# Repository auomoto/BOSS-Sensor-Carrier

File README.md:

# BOSS Sensor Carrier
## AD590 and HiH4031 Sensor Carrier
An AD590 temperature sensor and an HiH4031 humidity sensor are mounted on a single carrier board that also has a clearance hole for an 8-32 machine screw. These sensor boards are mounted at various locations inside the BOSS spectrograph.

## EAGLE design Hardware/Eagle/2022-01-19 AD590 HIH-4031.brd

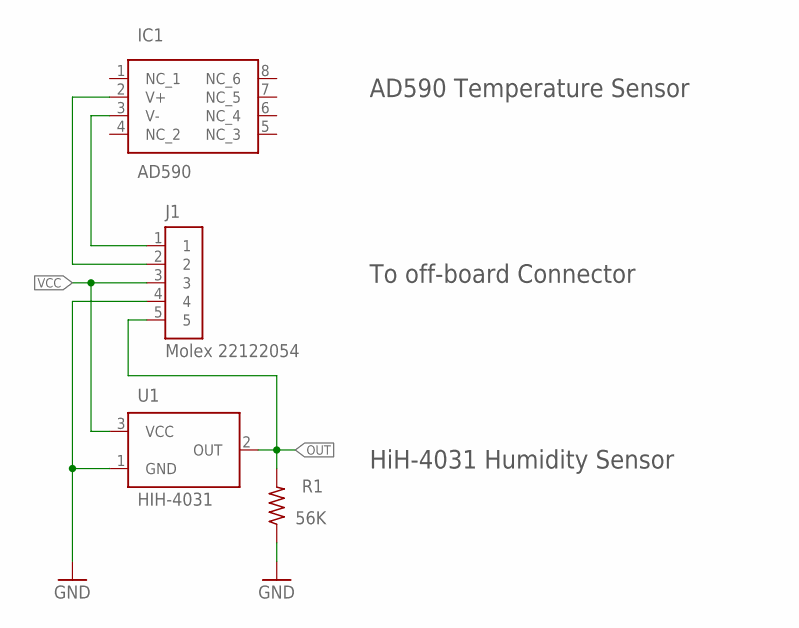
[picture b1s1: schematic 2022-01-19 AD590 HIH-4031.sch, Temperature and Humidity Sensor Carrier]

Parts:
IC1: AD590; SOIC127P600X175-8N
J1: Molex 22122054; 1X05RA-MOLEX-22122054
R1: 56K; R0805
U1: HIH-4031; HIH-4030

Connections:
GND: J1.4, R1.1, U1.1 (GND)
OUT: J1.5, R1.2, U1.2 (OUT)
V+: IC1.2 (V+), J1.2
V-: IC1.3 (V-), J1.1
VCC: J1.3, U1.3 (VCC)

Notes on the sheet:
AD590 Temperature Sensor
HiH-4031 Humidity Sensor
To off-board Connector

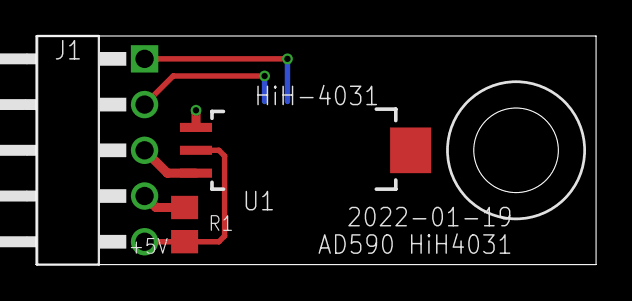
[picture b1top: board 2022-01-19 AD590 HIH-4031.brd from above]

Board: 2 copper layers, 31.1 x 12.7 mm, 4 parts (1 on the bottom side), 5 nets.

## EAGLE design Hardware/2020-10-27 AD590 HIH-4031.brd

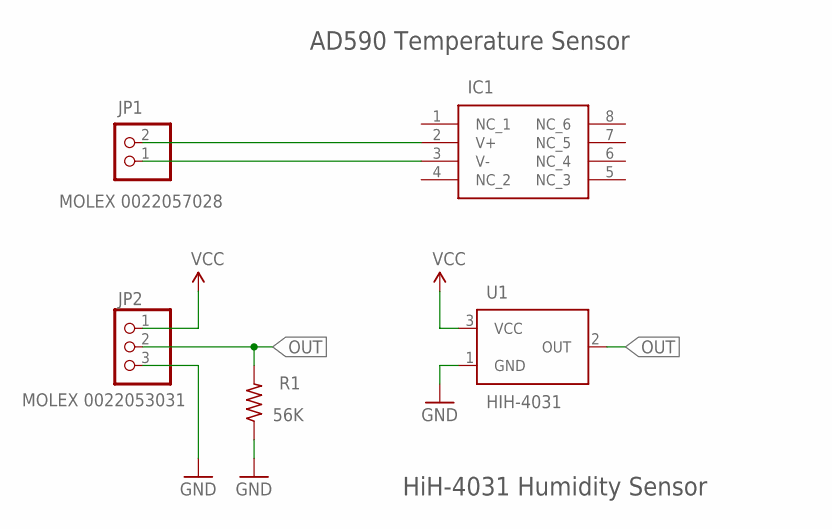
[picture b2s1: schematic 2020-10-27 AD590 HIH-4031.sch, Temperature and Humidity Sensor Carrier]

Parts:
IC1: AD590JRZ; SOIC127P600X175-8N
JP1: MOLEX 0022057028; MOLEX-7395-02-90DEG
JP2: MOLEX 0022053031; MOLEX-7395-03-90DEG
R1: 56K; R0805
U1: HIH-4031; HIH-4030

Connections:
GND: JP2.3, R1.1, U1.1 (GND)
OUT: JP2.2, R1.2, U1.2 (OUT)
V+: IC1.2 (V+), JP1.2
V-: IC1.3 (V-), JP1.1
VCC: JP2.1, U1.3 (VCC)

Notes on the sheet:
AD590 Temperature Sensor
HiH-4031 Humidity Sensor

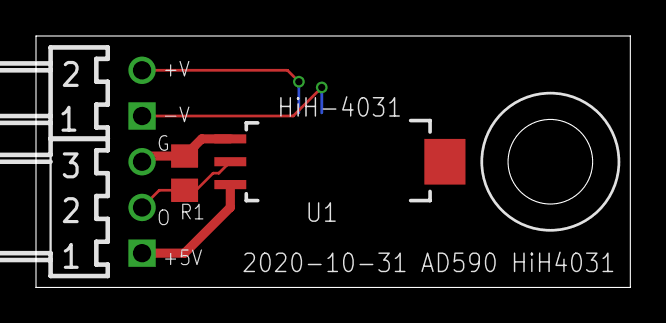
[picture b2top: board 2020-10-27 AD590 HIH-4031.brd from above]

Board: 2 copper layers, 33.0 x 14.0 mm, 5 parts (1 on the bottom side), 5 nets.

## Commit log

2020-10-27 Added Eagle board files
2020-10-27 Added tplace labels on front side
2020-10-31 Moved connectors to butt against each other
2021-01-05 Save minor changes
2021-01-24 Removed Eagle backup files
2021-01-24 Touched the schematic to test gitignore file
2021-01-24 Testing gitignore again
2021-02-20 Minor edits?
2021-07-24 Production
2022-06-14 Fix labeling on the back
